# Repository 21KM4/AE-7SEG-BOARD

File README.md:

# AE-7SEG-BOARD

７セグメントＬＥＤシリアルドライバキット

パラレル出力の抵抗は220Ωです。供給電圧や必要な光度に応じて調整してください。3.3V駆動ならちょうど良い明るさですが、5V駆動の場合は明るすぎると思います。
また、3.3Vでも緑色だと目がおかしくなるほどほど明るくなるので注意。予め7セグを買ってどの抵抗値がちょうどよいかは確認しておくと良いでしょう。

JLCPCB用のガーバーと部品配置もあります

参考にした製品：https://akizukidenshi.com/catalog/g/gK-10194/

上の製品とほぼ同じ回路で、抵抗値だけ変えています。この製品買うより自作して発注した方が安く済んじゃうので...

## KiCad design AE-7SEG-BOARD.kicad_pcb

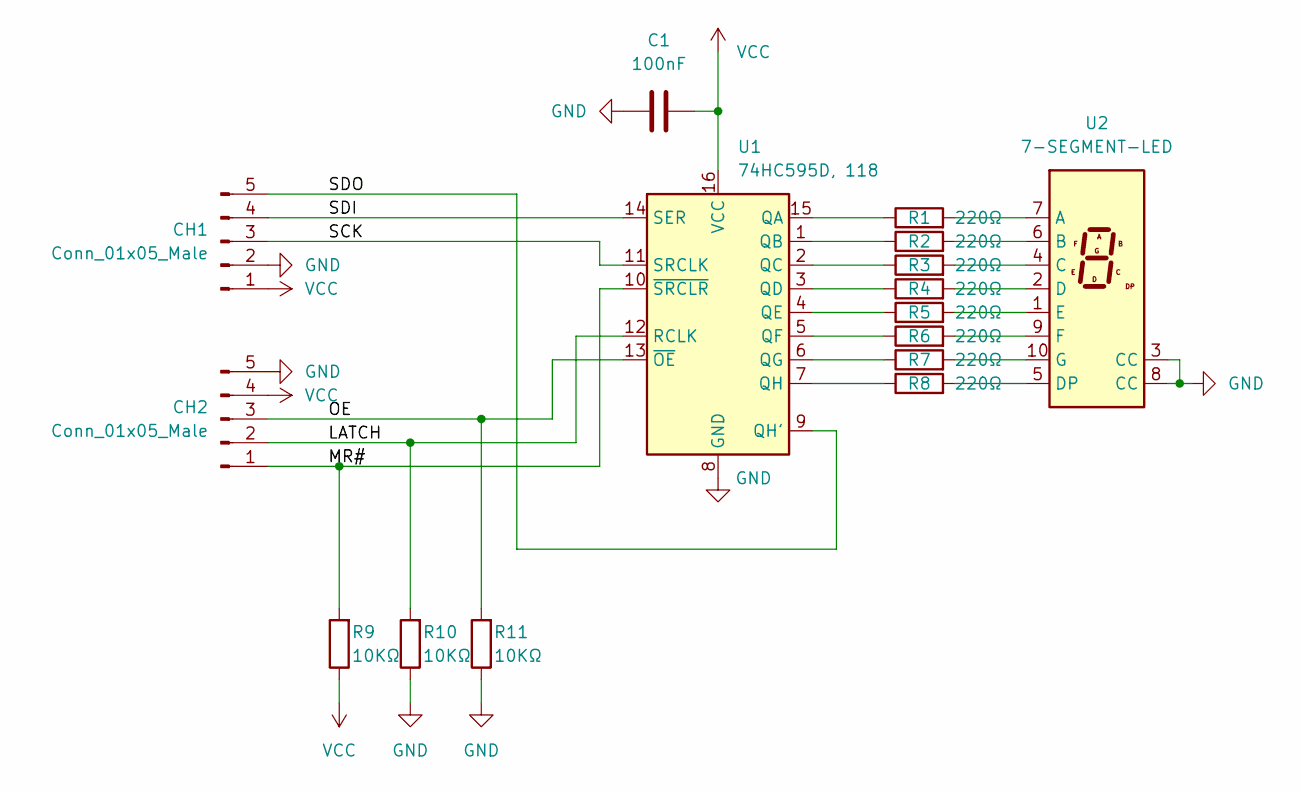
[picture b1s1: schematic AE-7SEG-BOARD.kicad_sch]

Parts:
C1: 100nF; C_0402_1005Metric; LCSC C1525
CH1, CH2: Conn_01x05_Male; PinHeader_1x05_P2.54mm_Vertical
R1, R2, R3, R4, R5, R6, R7, R8: 220Ω; R_0402_1005Metric; LCSC C25091
R9, R10, R11: 10KΩ; R_0402_1005Metric; LCSC C25744
U1: 74HC595D, 118; SOIC-16_3.9x9.9mm_P1.27mm; LCSC C5947
U2: 7-SEGMENT-LED; D1X8K

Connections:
/LATCH: CH2.2, R10.2, U1.12 (RCLK)
/MR#: CH2.1, R9.2, U1.10 (~SRCLR)
/OE: CH2.3, R11.2, U1.13 (~OE)
/SCK: CH1.3, U1.11 (SRCLK)
/SDI: CH1.4, U1.14 (SER)
/SDO: CH1.5, U1.9 (QH')
GND: C1.1, CH1.2, CH2.5, R10.1, R11.1, U1.8 (GND), U2.3 (CC), U2.8 (CC)
unnamed: R1.1, U1.15 (QA)
unnamed: R2.1, U1.1 (QB)
unnamed: R3.1, U1.2 (QC)
unnamed: R4.1, U1.3 (QD)
unnamed: R5.1, U1.4 (QE)
unnamed: R6.1, U1.5 (QF)
unnamed: R7.1, U1.6 (QG)
unnamed: R8.1, U1.7 (QH)
unnamed: R1.2, U2.7 (A)
unnamed: R2.2, U2.6 (B)
unnamed: R3.2, U2.4 (C)
unnamed: R4.2, U2.2 (D)
unnamed: R8.2, U2.5 (DP)
unnamed: R5.2, U2.1 (E)
unnamed: R6.2, U2.9 (F)
unnamed: R7.2, U2.10 (G)
VCC: C1.2, CH1.1, CH2.4, R9.1, U1.16 (VCC)

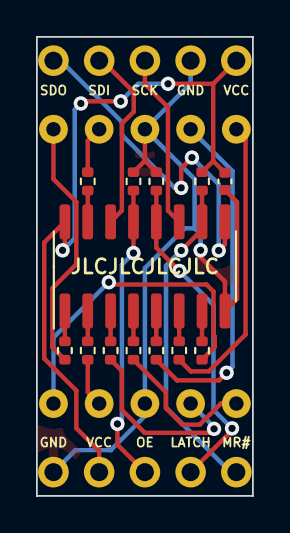
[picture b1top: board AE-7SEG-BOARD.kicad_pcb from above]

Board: 2 copper layers, 12.0 x 25.5 mm, 16 parts (1 on the bottom side), 24 nets.

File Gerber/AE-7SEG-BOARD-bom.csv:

"100nF","C1","Capacitor_SMD:C_0402_1005Metric","C1525"
"220Ω","R1,R2,R3,R4,R5,R6,R7,R8","Resistor_SMD:R_0402_1005Metric","C25091"
"10KΩ","R9,R10,R11","Resistor_SMD:R_0402_1005Metric","C25744"
"74HC595D, 118","U1","Package_SO:SOIC-16_3.9x9.9mm_P1.27mm","C5947"

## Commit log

2022-11-08 Create LICENSE
